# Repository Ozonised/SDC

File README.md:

# SDC

ATmega 8 based self driving car.

Watch the [YouTube](https://studio.youtube.com/video/CVWcEM45d_U/edit) video to develop some comprehension.

# SETTING UP ATMEGA 8
The ATmega 8 is programmed using an ICSP programmer. In my case, I used an Arduino UNO as an ICSP programmer.
By default, the microcontroller uses the internal 8MHz internal PC oscillator, but we want to use an external 16 MHz oscillator.
So we need to make certain changes to the fuse bits of the ATmega 8. Below are the steps to do so:
1. Download and install AVRDude. AVRDude is the program used by Arduino IDE and PlatformIO to upload your code to an AVR microcontroller.
2. Open up the Arduino IDE, select ```ArduinoISP``` under File/Examples/ and hit upload.
3. Wire up the Arduino and ATmega8 as shown in the [schematic](/Programmer/ATmega8-programmer.pdf): 
4. By default, the low fuse of the ATmega8 is set to 0xE1. This must be set to 0xE4 to configure the microcontroller to run at 8MHz. Type ``` avrdude -c stk500v1  -P COM5 -p atmega8 -b 19200 -U lfuse:w:0xe4:m -U hfuse:w:0xd9:m ```. Alternatively, you can use an online [AVR fuse bit calculator](https://www.engbedded.com/fusecalc/) for your selected microcontroller. 
### Note: 
The ```-P <port>```argument specifies the connection port. In my case, the arduino is connected to ```COM5``` and hence the argument ```-P COM5```. For ```-p <partno>``` either ```-p m8``` or ```-p atmega8``` can be used. Refer this [guide](https://www.ladyada.net/learn/avr/avrdude.html) for more information.

5. That is all. The ATmega8 is now ready to be programmed with PlatformIO using the arduino as an ISP programmer.

# PART LIST:
You can find the component list [here](SDC_Schematic/SDC_Schematic.csv).

The case along with the motor is available here: https://quartzcomponents.com/products/2wd-smart-robot-car-chassis-kit

MOC7811 optical encoders: https://quartzcomponents.com/products/moc-7811-encoder-sensor

Servo: https://quartzcomponents.com/products/tower-pro-sg90-servo-9-gms-mini-micro-servo-motor?_pos=1&_sid=c2dd11a64&_ss=r

HCSR04(Ultrasonic sensor): https://quartzcomponents.com/products/hc-sr04-ultrasonic-sensor-module?_pos=1&_sid=1f37cc7e0&_ss=r

Ultrasonic sensor mount: https://quartzcomponents.com/products/ultrasonic-sensor-mounting-bracket-for-hc-sr04?_pos=3&_sid=1f37cc7e0&_ss=r

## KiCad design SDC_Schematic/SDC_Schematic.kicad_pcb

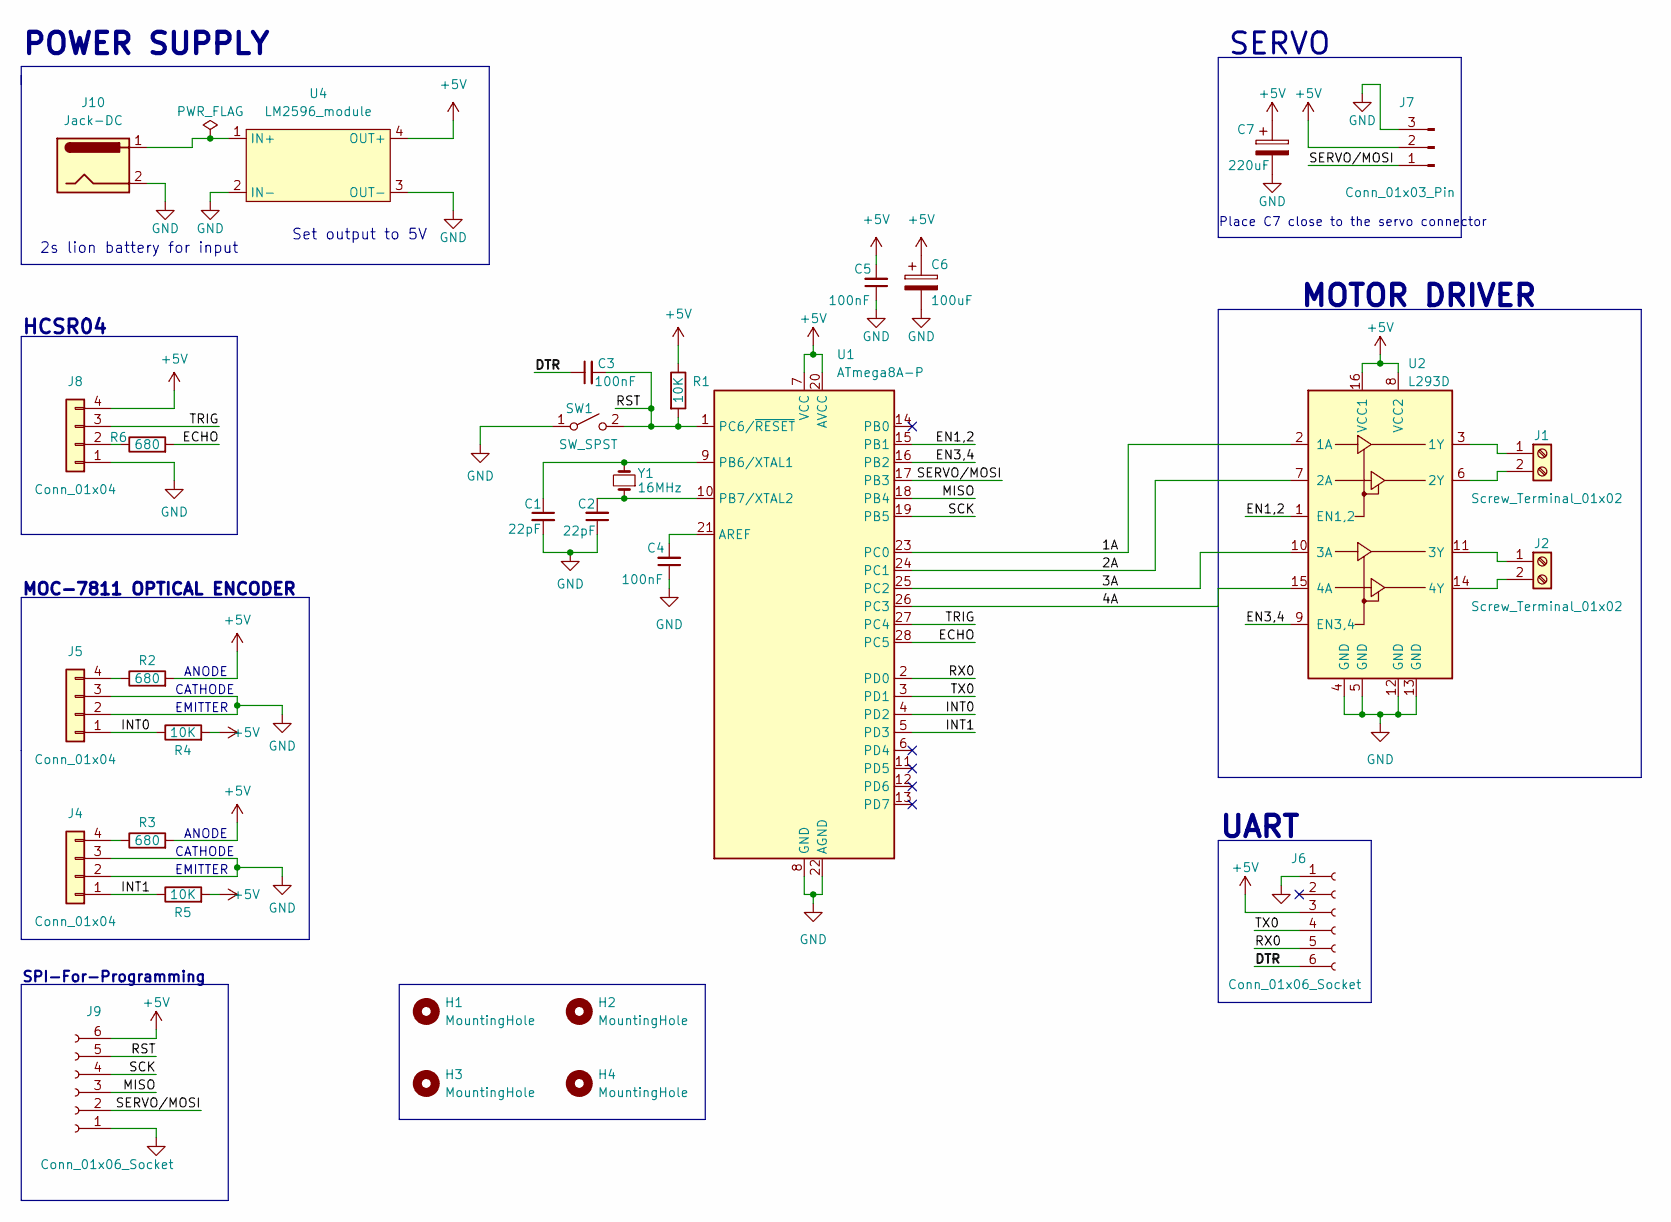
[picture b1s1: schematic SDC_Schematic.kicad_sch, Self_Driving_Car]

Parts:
C1, C2: 22pF; C_Disc_D3.0mm_W2.0mm_P2.50mm
C3, C4, C5: 100nF; C_Disc_D5.0mm_W2.5mm_P2.50mm
C6: 100uF; CP_Radial_D6.3mm_P2.50mm
C7: 220uF; CP_Radial_D6.3mm_P2.50mm
H1, H2, H3, H4: MountingHole; MountingHole_3.5mm
J1, J2: Screw_Terminal_01x02; TerminalBlock_Altech_AK300-2_P5.00mm
J4, J5, J8: Conn_01x04; PinSocket_1x04_P2.54mm_Vertical
J6, J9: Conn_01x06_Socket; PinSocket_1x06_P2.54mm_Vertical
J7: Conn_01x03_Pin; PinHeader_1x03_P2.54mm_Vertical
J10: Jack-DC; BarrelJack_Horizontal
R1, R4, R5: 10K; R_Axial_DIN0207_L6.3mm_D2.5mm_P7.62mm_Horizontal
R2, R3, R6: 680; R_Axial_DIN0207_L6.3mm_D2.5mm_P7.62mm_Horizontal
SW1: SW_SPST; SW_PUSH_6mm_H4.3mm
U1: ATmega8A-P; DIP-28_W7.62mm
U2: L293D; DIP-16_W7.62mm
U4: LM2596_module
Y1: 16MHz; Crystal_HC49-4H_Vertical

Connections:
+5V: C5.2, C6.1, C7.1, J6.3, J7.2, J8.4, J9.6, R1.1, R2.2, R3.2, R4.2, R5.2, U1.7 (VCC), U1.20 (AVCC), U2.8 (VCC2), U2.16 (VCC1), U4.4 (OUT+)
/1A: U1.23 (PC0), U2.2 (1A)
/2A: U1.24 (PC1), U2.7 (2A)
/3A: U1.25 (PC2), U2.10 (3A)
/4A: U1.26 (PC3), U2.15 (4A)
/DTR: C3.1, J6.6
/ECHO: R6.2, U1.28 (PC5)
/EN1,2: U1.15 (PB1), U2.1 (EN1,2)
/EN3,4: U1.16 (PB2), U2.9 (EN3,4)
/INT0: J5.1, R4.1, U1.4 (PD2)
/INT1: J4.1, R5.1, U1.5 (PD3)
/MISO: J9.3, U1.18 (PB4)
/RST: C3.2, J9.5, R1.2, SW1.2 (B), U1.1 (PC6/~RESET)
/RX0: J6.5, U1.2 (PD0)
/SCK: J9.4, U1.19 (PB5)
/SERVO/MOSI: J7.1, J9.2, U1.17 (PB3)
/TRIG: J8.3, U1.27 (PC4)
/TX0: J6.4, U1.3 (PD1)
GND: C1.2, C2.1, C4.1, C5.1, C6.2, C7.2, J4.2, J4.3, J5.2, J5.3, J6.1, J7.3, J8.1, J9.1, J10.2, SW1.1 (A), U1.8 (GND), U1.22 (AGND), U2.4 (GND), U2.5 (GND), U2.12 (GND), U2.13 (GND), U4.2 (IN-), U4.3 (OUT-)
unnamed: J1.1, U2.3 (1Y)
unnamed: J1.2, U2.6 (2Y)
unnamed: J2.1, U2.11 (3Y)
unnamed: J2.2, U2.14 (4Y)
unnamed: J4.4, R3.1
unnamed: J5.4, R2.1
unnamed: J8.2, R6.1
unnamed: C4.2, U1.21 (AREF)
unnamed: C1.1, U1.9 (PB6/XTAL1), Y1.2
unnamed: C2.2, U1.10 (PB7/XTAL2), Y1.1
unnamed: J10.1, U4.1 (IN+)

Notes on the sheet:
HCSR04
Set output to 5V
SPI-For-Programming
MOTOR DRIVER
2s lion battery for input
EMITTER
ANODE
SERVO
Place C7 close to the servo connector
CATHODE
POWER SUPPLY
MOC-7811 OPTICAL ENCODER
UART

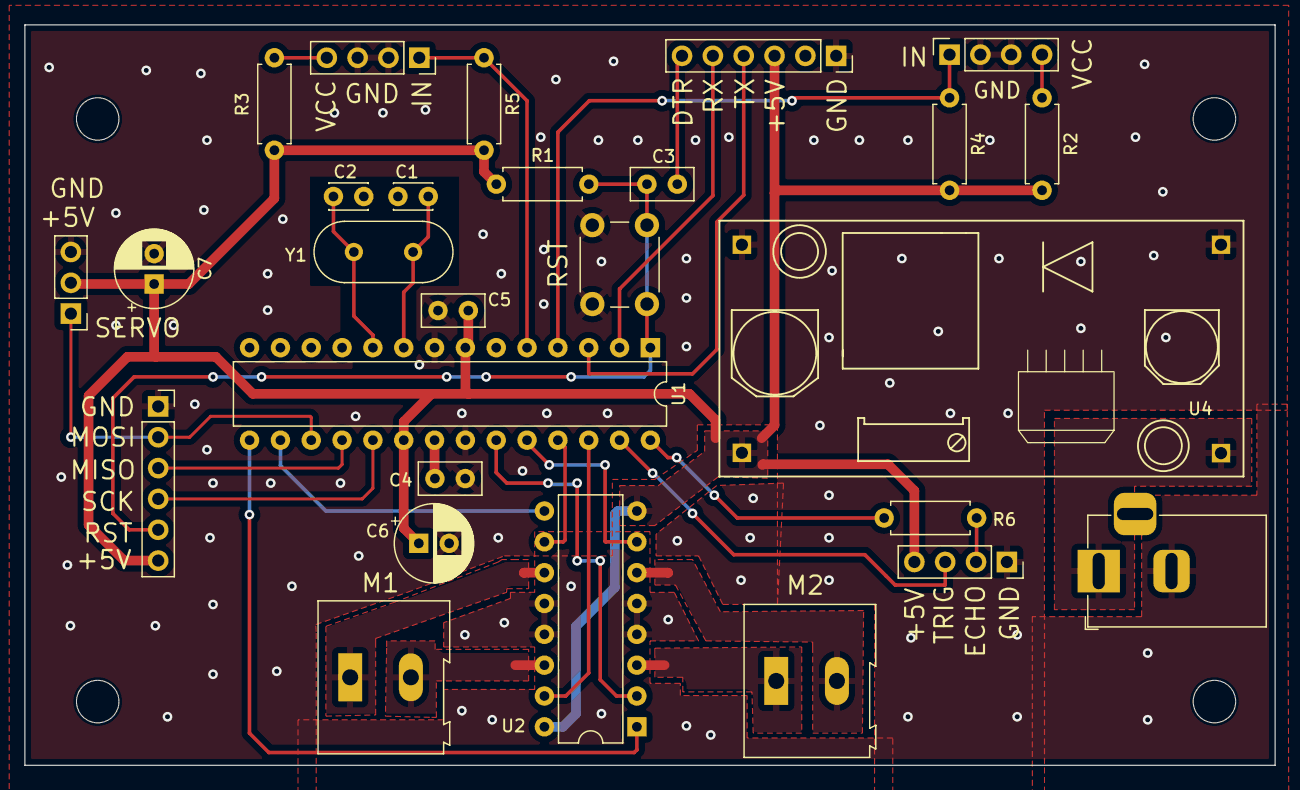
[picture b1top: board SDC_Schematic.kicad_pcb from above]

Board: 2 copper layers, 103.0 x 61.0 mm, 31 parts (0 on the bottom side), 30 nets.

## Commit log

2023-07-19 added image
2023-07-19 Programer
    added schematic for programming the ATmega 8
2023-07-19 Update README.md
    Added steps to program the ATmega 8
2023-07-19 modified schematic
    added SPI port, capacitors for the servo & uC and barrel jack for power input
2023-07-19 added part list
2023-07-20 added mounting hole
2023-09-02 Schematic and PCB
    updated schematic symbols and connections as well as created a PCB along with gerber files
2023-09-02 L293d driver
    made correction to left and right direction control
2023-10-06 modified PCB and schematic
2023-10-06 updated schematic and PCB
2023-10-06 added PID lib
2023-10-08 added a default constructor & some fixes
2023-10-14 class member order
    changed the order of public members as per member init list
2023-10-14 modified gitignore
2023-10-14 renamed scanDistance to scanArea
2023-10-14 modified servoSet
    fixed issue where the servo wouldn't turn 180 and 0 completely
2023-10-15 modified servo and l293d lib
    placed servo's and motor's init and move function in their respective namespaces
2023-10-16 made prevError public
2023-10-19 added motor count for each motor
2023-10-19 minor changes to member init list
2023-10-19 removed unnecessary include files
2023-10-19 modified drive scanArea & added PID_init
    added pid control for driving forward and making turns
    Condensed scanArea()
2024-01-22 updated thumbnail
